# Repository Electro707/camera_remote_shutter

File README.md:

# Camera Remote Shutter Project
#### Rev 1.0-alpha

This is an open-source camera remote shutter.

## Enclosure
There is a work-in-progress enclosure for the PCB under the [CAD](CAD) folder. The enclosure is made with FreeCAD 0.20.

## Firmware
The firmware for this project is in the `AVR` folder. To build the code, simply run

```
make
```

This will generate a binary to upload to the MCU. To program the board, you can connect an Arduino Uno acting as an ISP device to the 3x2 connector on the board (J2). Then you can use the following make argument to upload with AVRDude. The port is asssumed to be `/dev/ttyUSB0`, so if that is different you can change the makefile.

```
make program
```

## KiCAD 3D Models
The 3D models for some components in the directory `PCB/3d_model/` are not included due to licensing reasons. You can grab the step files yourself and put it in that directory from the manufacturer. The models are
- 12CE3H26F12T24.stp
- CUI_DEVICES_SJ-2509N.step

# License
This project is licensed under GPLv3. See [LICENSE.md](LICENSE.md) for details.

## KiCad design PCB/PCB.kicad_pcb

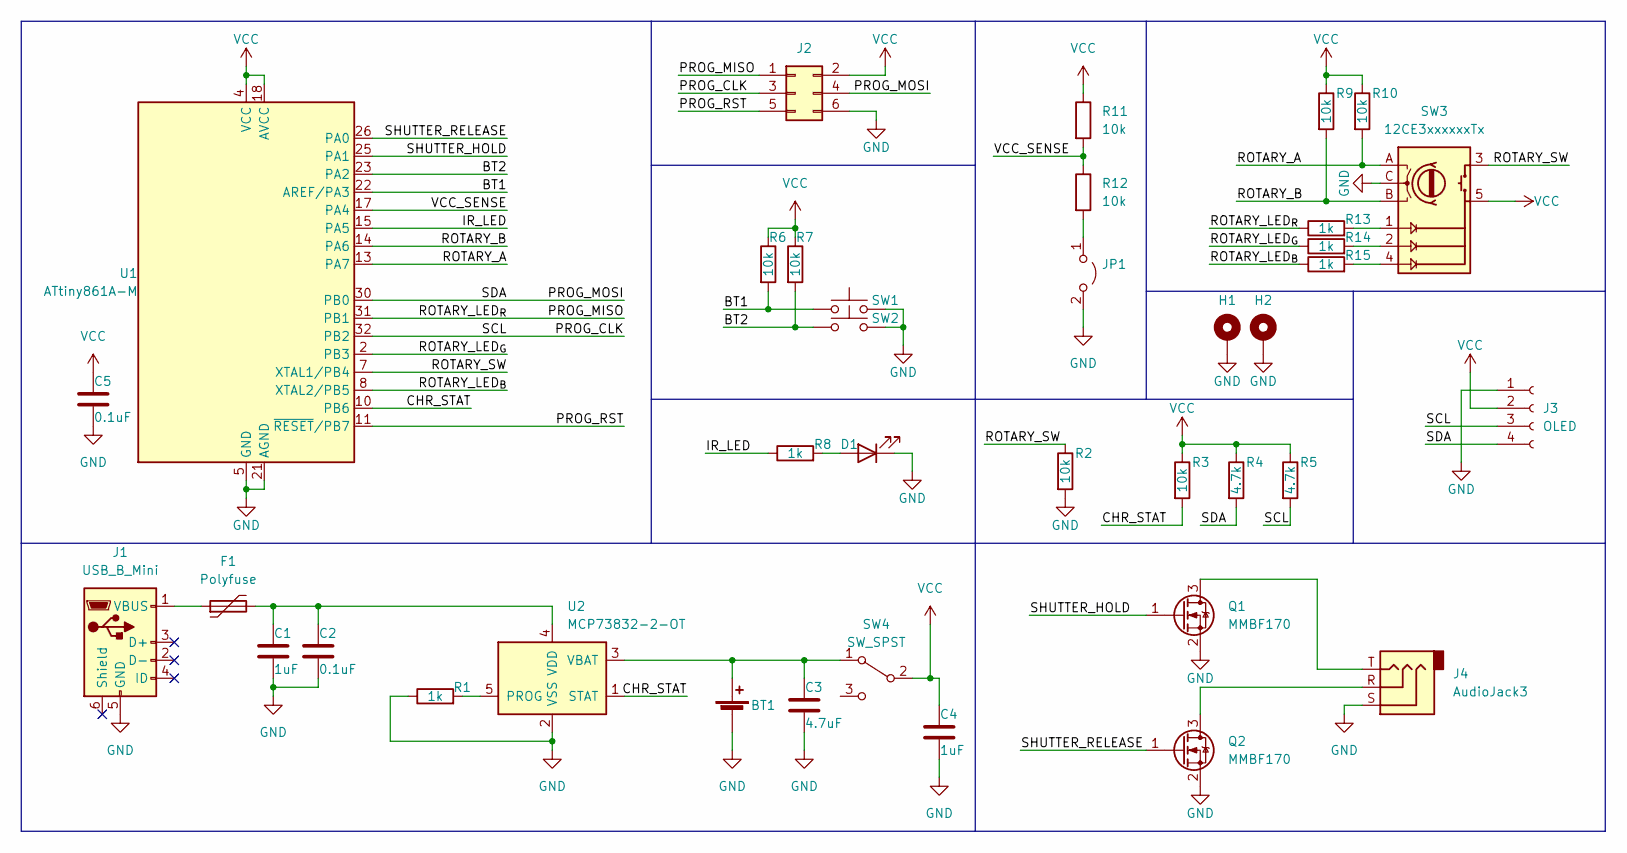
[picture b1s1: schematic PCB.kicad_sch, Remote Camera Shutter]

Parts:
BT1: Battery_Cell; PinSocket_1x02_P2.54mm_Vertical
C1, C4: 1uF; C_0805_2012Metric_Pad1.18x1.45mm_HandSolder
C2, C5: 0.1uF; C_0805_2012Metric_Pad1.18x1.45mm_HandSolder
C3: 4.7uF; C_1206_3216Metric_Pad1.33x1.80mm_HandSolder
D1: LED; LED_D5.0mm_Horizontal_O3.81mm_Z3.0mm
F1: Polyfuse; Fuse_1210_3225Metric_Pad1.42x2.65mm_HandSolder
H1, H2: MountingHole_Pad; MountingHole_3.2mm_M3_DIN965_Pad
J1: USB_B_Mini; USB_Micro-B_Wuerth_629105150521
J2: Conn_02x03_Odd_Even; PinSocket_2x03_P2.54mm_Vertical
J3: OLED; PinSocket_1x04_P2.54mm_Vertical
J4: AudioJack3; MJ1-2503A
JP1: Jumper_2_Open; SolderJumper-2_P1.3mm_Open_RoundedPad1.0x1.5mm
Q1, Q2: MMBF170; SOT-23
R1, R8, R13, R14, R15: 1k; R_0805_2012Metric_Pad1.20x1.40mm_HandSolder
R2, R3, R6, R7, R9, R10, R11, R12: 10k; R_0805_2012Metric_Pad1.20x1.40mm_HandSolder
R4, R5: 4.7k; R_0805_2012Metric_Pad1.20x1.40mm_HandSolder
SW1, SW2: SW_Push; SW_PUSH_6mm
SW3: 12CE3xxxxxxTx; 12CE3KxxxxxTx
SW4: SW_SPST; SW_SPDT_PCM12
U1: ATtiny861A-M; QFN-32-1EP_5x5mm_P0.5mm_EP3.1x3.1mm
U2: MCP73832-2-OT; SOT-23-5

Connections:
/BT1: R6.2, SW1.1, U1.22 (AREF/PA3)
/BT2: R7.2, SW2.1, U1.23 (PA2)
/CHR_STAT: R3.2, U1.10 (PB6), U2.1 (STAT)
/IR_LED: R8.1, U1.15 (PA5)
/PROG_CLK: J2.3, J3.3, R5.2, U1.32 (PB2)
/PROG_MISO: J2.1, R13.1, U1.31 (PB1)
/PROG_MOSI: J2.4, J3.4, R4.2, U1.30 (PB0)
/PROG_RST: J2.5, U1.11 (~RESET/PB7)
/ROTARY_A: R10.2, SW3.A, U1.13 (PA7)
/ROTARY_B: R9.2, SW3.B, U1.14 (PA6)
/ROTARY_LED_{B}: R15.1, U1.8 (XTAL2/PB5)
/ROTARY_LED_{G}: R14.1, U1.2 (PB3)
/ROTARY_SW: R2.1, SW3.3 (S1), U1.7 (XTAL1/PB4)
/SHUTTER_HOLD: Q1.1 (G), U1.25 (PA1)
/SHUTTER_RELEASE: Q2.1 (G), U1.26 (PA0)
/VCC_SENSE: R11.2, R12.1, U1.17 (PA4)
GND: BT1.2 (-), C1.2, C2.2, C3.2, C4.2, C5.2, D1.1 (K), H1.1, H2.1, J1.5 (GND), J2.6, J3.1, J4.S, JP1.2 (B), Q1.2 (S), Q2.2 (S), R1.1, R2.2, SW1.2, SW2.2, SW3.C, U1.5 (GND), U1.21 (AGND), U1.33 (GND), U2.2 (VSS)
unnamed: BT1.1 (+), C3.1, SW4.1 (A), U2.3 (VBAT)
unnamed: D1.2 (A), R8.2
unnamed: F1.1, J1.1 (VBUS)
unnamed: JP1.1 (A), R12.2
unnamed: J4.T, Q1.3 (D)
unnamed: J4.R, Q2.3 (D)
unnamed: R15.2, SW3.4 (L_B)
unnamed: R14.2, SW3.2 (L_G)
unnamed: R13.2, SW3.1 (L_R)
unnamed: R1.2, U2.5 (PROG)
unnamed: C1.1, C2.1, F1.2, U2.4 (VDD)
VCC: C4.1, C5.1, J2.2, J3.2, R3.1, R4.1, R5.1, R6.1, R7.1, R9.1, R10.1, R11.1, SW3.5 (COMM), SW4.2 (B), U1.4 (VCC), U1.18 (AVCC)

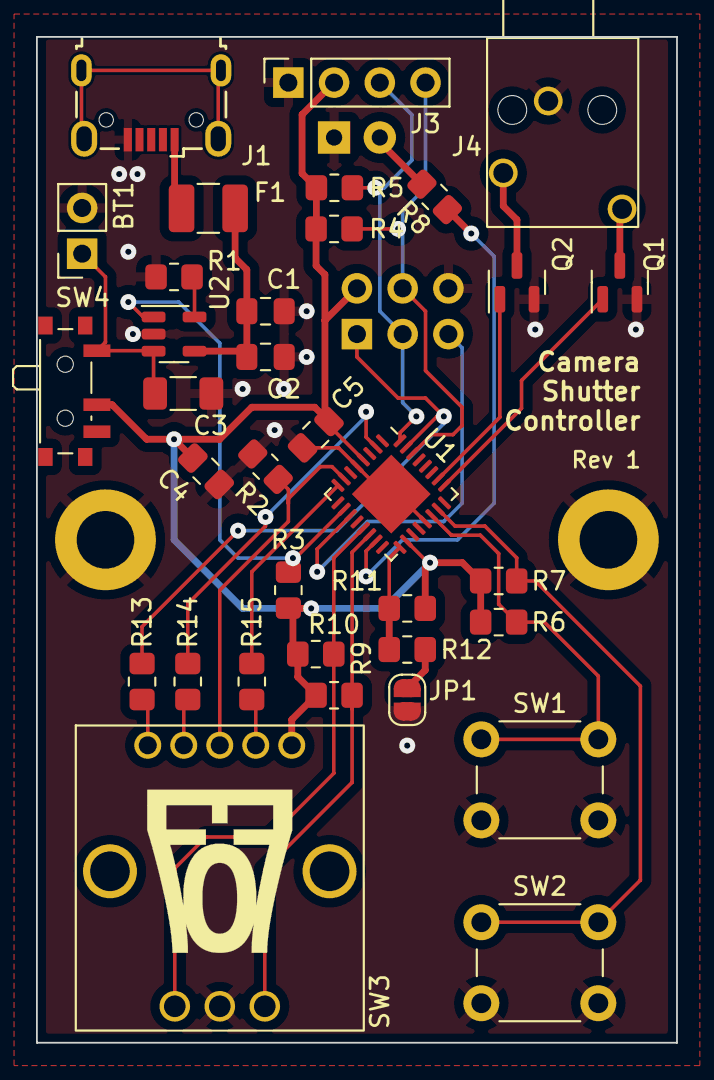
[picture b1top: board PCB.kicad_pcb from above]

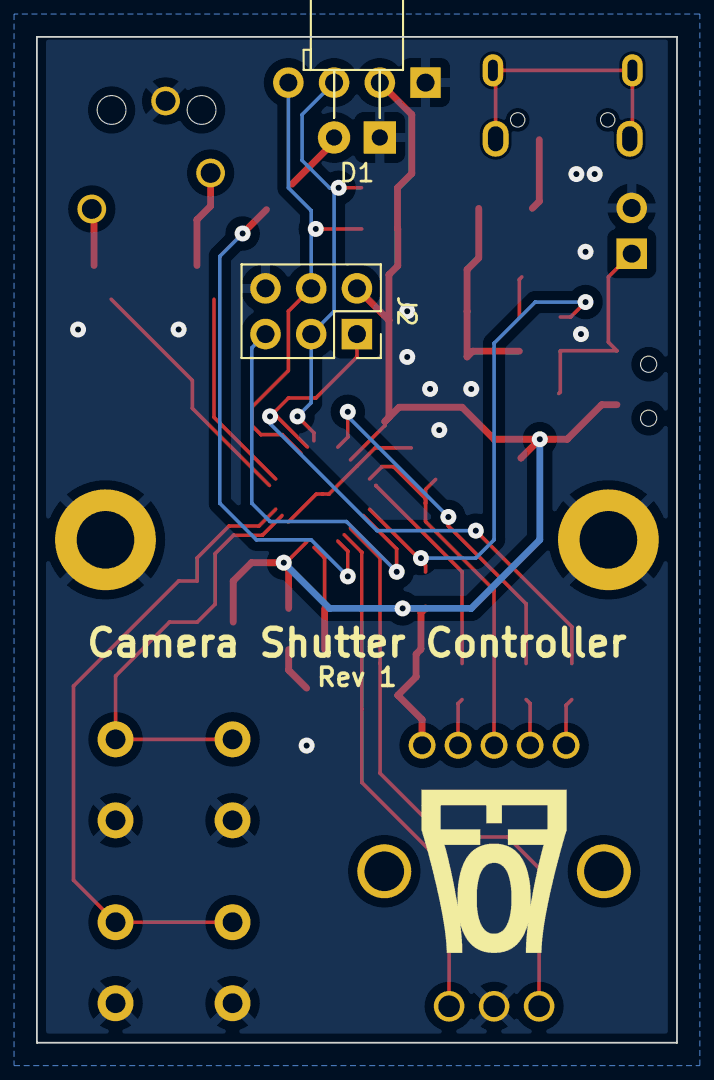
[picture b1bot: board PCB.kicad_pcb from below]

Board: 2 copper layers, 35.6 x 55.9 mm, 38 parts (2 on the bottom side), 29 nets.

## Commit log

2022-04-06 Finally got it to a working state
2022-04-06 Updated schematic
2022-04-18 Added a WIP CAD model
2022-09-13 Finished initial design of enclosure. Added dimentions to PCB
2022-10-02 Updated top cover. Added picture
2023-10-17 Save poinit with firmware. Added LICENSE
2023-10-17 Added timelapse mode, some variable re-work
2023-10-17 Updated file headers
2024-07-02 Updated? pcb files. Modification to CAD. updated gitignore
2024-07-02 added battery level indicator trigger does both pins, which is needed for some cameras rotary encoder improvements more firmware improvements
